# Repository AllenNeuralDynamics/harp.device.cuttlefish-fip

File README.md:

A [Cuttlefish](https://github.com/AllenNeuralDynamics/harp.device.cuttlefish) adapted to a dedicated fiber photometry application.

## Waveform Parameter Overview
This firmware generates the waveform below.

Multiple parameters are configurable:
* Continuous, or iterations
* software-trigger to start waveform generation
* `EVENT` message emitted upon rising edge of any camera trigger (configurable)

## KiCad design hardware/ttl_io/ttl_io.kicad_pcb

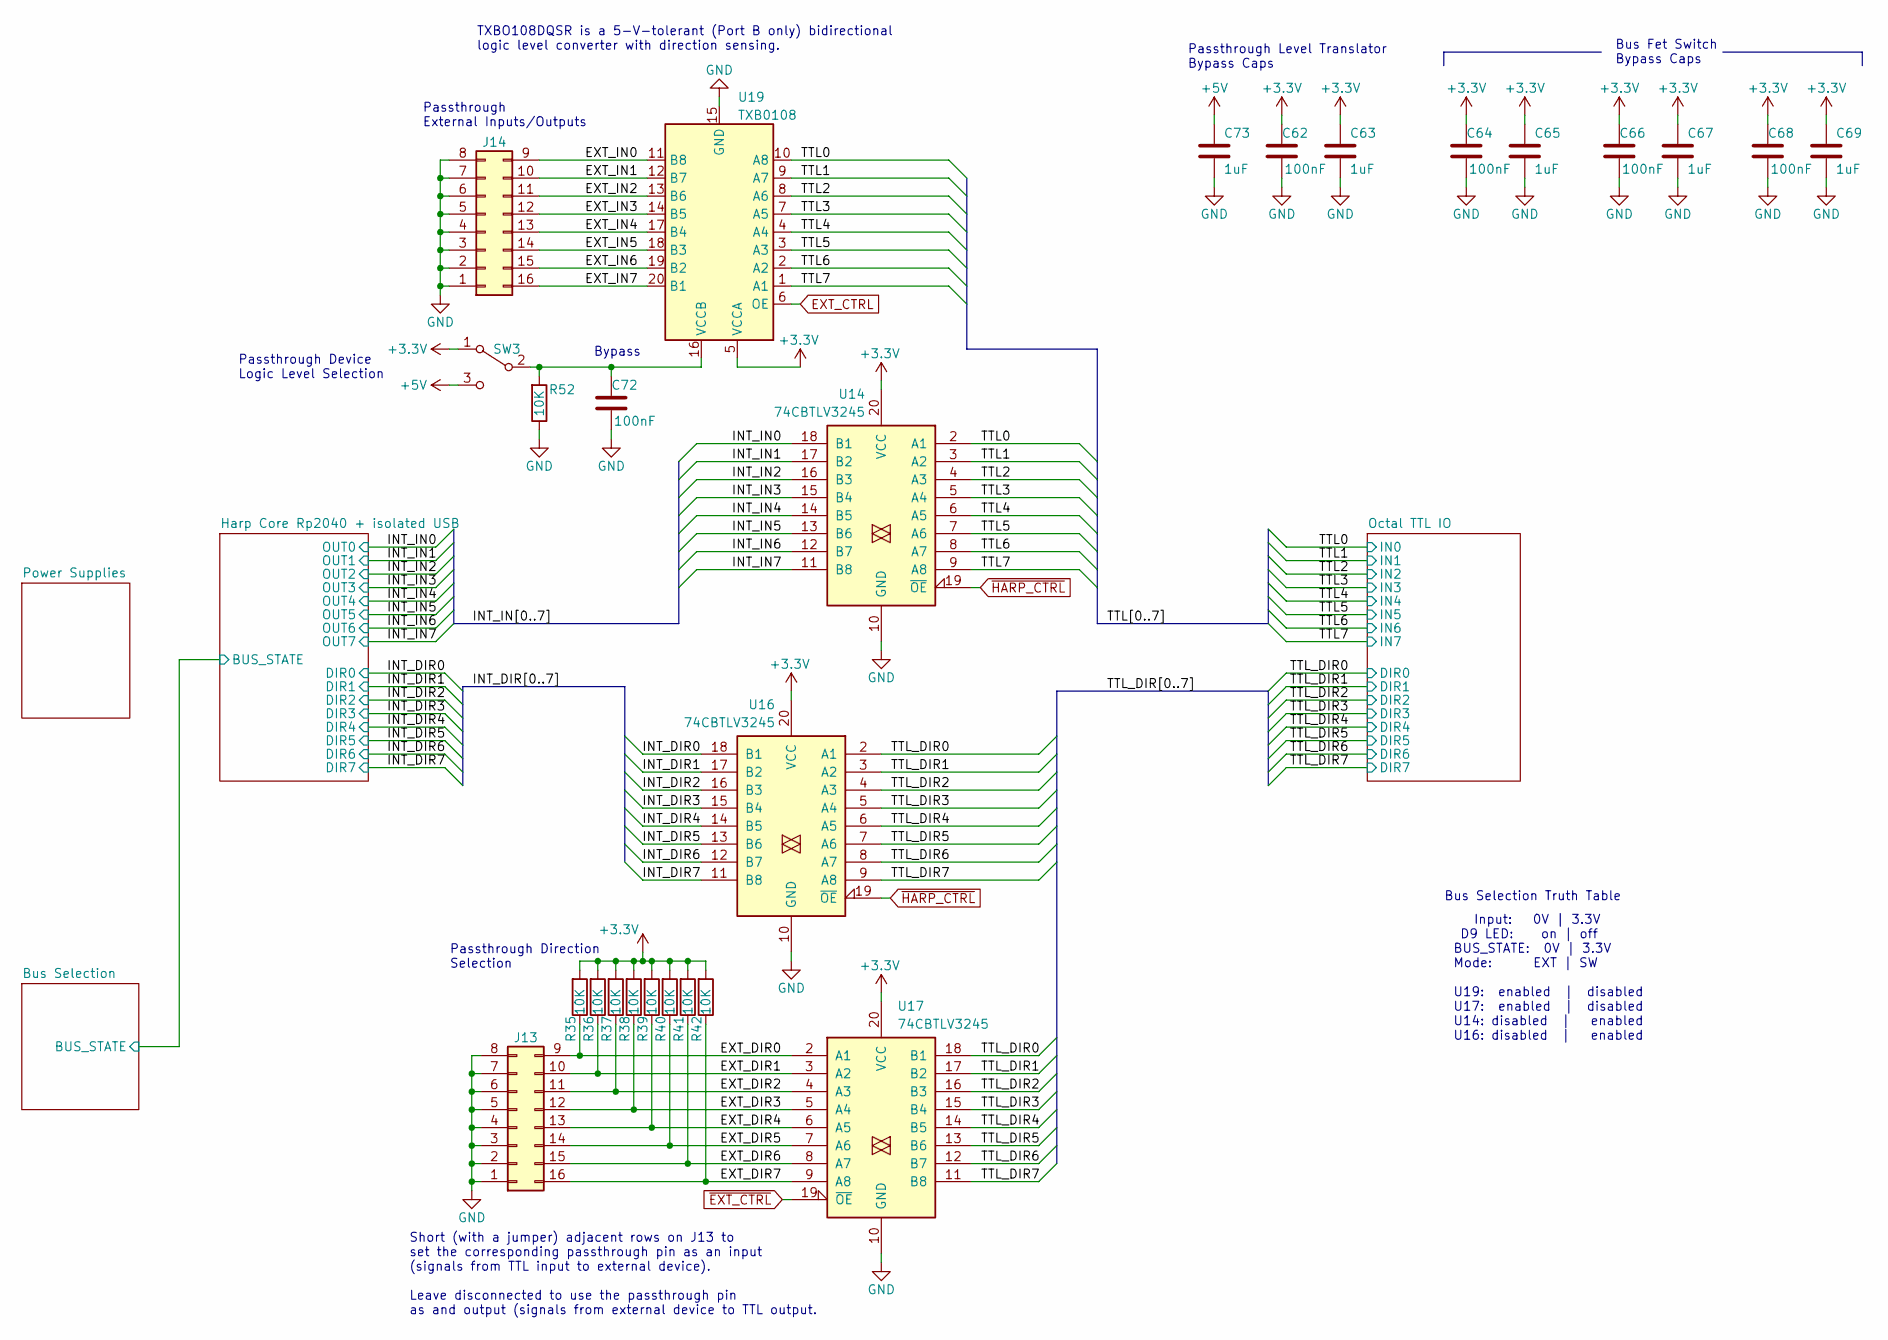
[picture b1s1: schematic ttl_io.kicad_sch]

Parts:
C62, C64, C66, C68, C72: 100nF; C_0402_1005Metric; Rated Voltage 16V; Tolerance 10%
C63, C65, C67, C69, C73: 1uF; C_0402_1005Metric; Rated Voltage 35V
J13, J14: Conn_02x08_Counter_Clockwise; PinHeader_2x08_P2.54mm_Horizontal_SMD
R35, R36, R37, R38, R39, R40, R41, R42, R52: 10K; R_0402_1005Metric
SW3: SW_SPDT; SW_SPDT_CK-JS102011SAQN
U14, U16, U17: 74CBTLV3245; TSSOP-20_4.4x6.5mm_P0.65mm
U19: TXB0108; TSSOP-20_4.4x6.5mm_P0.65mm

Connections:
+5V: C73.1, SW3.3 (C); also elsewhere on the board
/EXT_DIR0: J13.9, R35.1, U17.2 (A1)
/EXT_DIR1: J13.10, R36.1, U17.3 (A2)
/EXT_DIR2: J13.11, R37.1, U17.4 (A3)
/EXT_DIR3: J13.12, R38.1, U17.5 (A4)
/EXT_DIR4: J13.13, R39.1, U17.6 (A5)
/EXT_DIR5: J13.14, R40.1, U17.7 (A6)
/EXT_DIR6: J13.15, R41.1, U17.8 (A7)
/EXT_DIR7: J13.16, R42.1, U17.9 (A8)
/EXT_IN0: J14.9, U19.11 (B8)
/EXT_IN1: J14.10, U19.12 (B7)
/EXT_IN2: J14.11, U19.13 (B6)
/EXT_IN3: J14.12, U19.14 (B5)
/EXT_IN4: J14.13, U19.17 (B4)
/EXT_IN5: J14.14, U19.18 (B3)
/EXT_IN6: J14.15, U19.19 (B2)
/EXT_IN7: J14.16, U19.20 (B1)
/INT_DIR0: U16.18 (B1); also elsewhere on the board
/INT_DIR1: U16.17 (B2); also elsewhere on the board
/INT_DIR2: U16.16 (B3); also elsewhere on the board
/INT_DIR3: U16.15 (B4); also elsewhere on the board
/INT_DIR4: U16.14 (B5); also elsewhere on the board
/INT_DIR5: U16.13 (B6); also elsewhere on the board
/INT_DIR6: U16.12 (B7); also elsewhere on the board
/INT_DIR7: U16.11 (B8); also elsewhere on the board
/INT_IN0: U14.18 (B1); also elsewhere on the board
/INT_IN1: U14.17 (B2); also elsewhere on the board
/INT_IN2: U14.16 (B3); also elsewhere on the board
/INT_IN3: U14.15 (B4); also elsewhere on the board
/INT_IN4: U14.14 (B5); also elsewhere on the board
/INT_IN5: U14.13 (B6); also elsewhere on the board
/INT_IN6: U14.12 (B7); also elsewhere on the board
/INT_IN7: U14.11 (B8); also elsewhere on the board
/TTL0: U14.2 (A1), U19.10 (A8); also elsewhere on the board
/TTL1: U14.3 (A2), U19.9 (A7); also elsewhere on the board
/TTL2: U14.4 (A3), U19.8 (A6); also elsewhere on the board
/TTL3: U14.5 (A4), U19.7 (A5); also elsewhere on the board
/TTL4: U14.6 (A5), U19.4 (A4); also elsewhere on the board
/TTL5: U14.7 (A6), U19.3 (A3); also elsewhere on the board
/TTL6: U14.8 (A7), U19.2 (A2); also elsewhere on the board
/TTL7: U14.9 (A8), U19.1 (A1); also elsewhere on the board
/TTL_DIR0: U16.2 (A1), U17.18 (B1); also elsewhere on the board
/TTL_DIR1: U16.3 (A2), U17.17 (B2); also elsewhere on the board
/TTL_DIR2: U16.4 (A3), U17.16 (B3); also elsewhere on the board
/TTL_DIR3: U16.5 (A4), U17.15 (B4); also elsewhere on the board
/TTL_DIR4: U16.6 (A5), U17.14 (B5); also elsewhere on the board
/TTL_DIR5: U16.7 (A6), U17.13 (B6); also elsewhere on the board
/TTL_DIR6: U16.8 (A7), U17.12 (B7); also elsewhere on the board
/TTL_DIR7: U16.9 (A8), U17.11 (B8); also elsewhere on the board
EXT_CTRL: U19.6 (OE); also elsewhere on the board
GND: C62.1, C63.2, C64.1, C65.2, C66.1, C67.2, C68.1, C69.2, C72.1, C73.2, J13.1, J13.2, J13.3, J13.4, J13.5, J13.6, J13.7, J13.8, J14.1, J14.2, J14.3, J14.4, J14.5, J14.6, J14.7, J14.8, R52.1, U14.10 (GND), U16.10 (GND), U17.10 (GND), U19.15 (GND); also elsewhere on the board
unnamed: C72.2, R52.2, SW3.2 (B), U19.16 (VCCB)
~EXT_CTRL: U17.19 (~OE); also elsewhere on the board
~HARP_CTRL: U14.19 (~OE), U16.19 (~OE); also elsewhere on the board

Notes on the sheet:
Passthrough External Inputs/Outputs
Input: 0V | 3.3V D9 LED: on | off BUS_STATE: 0V | 3.3V Mode: EXT | SW U19: enabled | disabled U17: enabled | disabled U14: disabled | enabled U16: disabled | enabled
Passthrough Direction Selection
Bus Fet Switch Bypass Caps
TXBO108DQSR is a 5-V-tolerant (Port B only) bidirectional logic level converter with direction sensing.
Short (with a jumper) adjacent rows on J13 to set the corresponding passthrough pin as an input (signals from TTL input to external device). Leave disconnected to use the passthrough pin as and output (signals from external device to TTL output.
Passthrough Device Logic Level Selection
Bypass
Passthrough Level Translator Bypass Caps
Bus Selection Truth Table

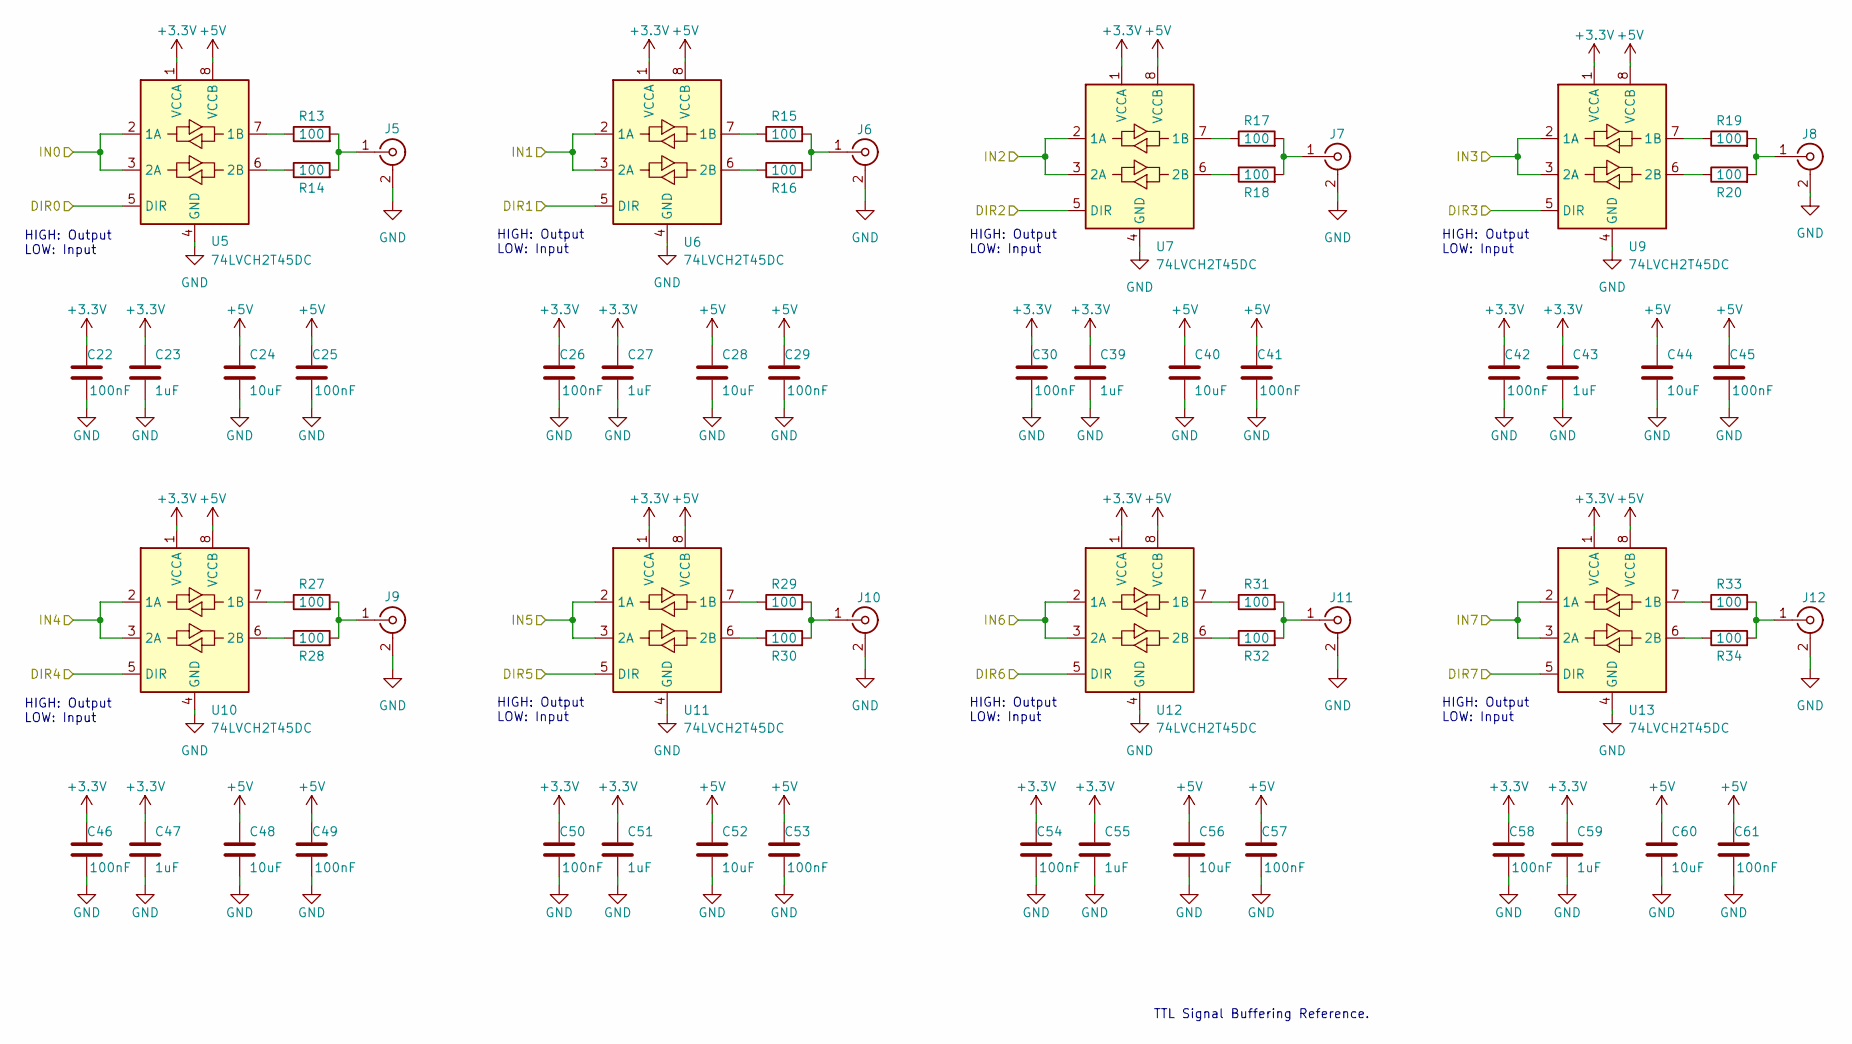
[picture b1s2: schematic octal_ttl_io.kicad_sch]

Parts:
C22, C25, C26, C29, C30, C41, C42, C45, C46, C49, C50, C53, C54, C57, C58, C61: 100nF; C_0402_1005Metric; Rated Voltage 16V; Tolerance 10%
C23, C27, C39, C43, C47, C51, C55, C59: 1uF; C_0402_1005Metric; Rated Voltage 35V
C24, C28, C40, C44, C48, C52, C56, C60: 10uF; C_0805_2012Metric; Rated Voltage 25V
J5, J6, J7, J8, J9, J10, J11, J12: Conn_Coaxial; BNC_AmphenolRF_031-5329-52RFX_Vertical
R13, R14, R15, R16, R17, R18, R19, R20, R27, R28, R29, R30, R31, R32, R33, R34: 100; R_0402_1005Metric; Tolerance 1%
U5, U6, U7, U9, U10, U11, U12, U13: 74LVCH2T45DC; VSSOP-8_2.3x2mm_P0.5mm

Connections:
+5V: C24.1, C25.2, C28.1, C29.2, C40.1, C41.2, C44.1, C45.2, C48.1, C49.2, C52.1, C53.2, C56.1, C57.2, C60.1, C61.2, U5.8 (VCCB), U6.8 (VCCB), U7.8 (VCCB), U9.8 (VCCB), U10.8 (VCCB), U11.8 (VCCB), U12.8 (VCCB), U13.8 (VCCB); also elsewhere on the board
/TTL0: U5.2 (1A), U5.3 (2A); also elsewhere on the board
/TTL1: U6.2 (1A), U6.3 (2A); also elsewhere on the board
/TTL2: U7.2 (1A), U7.3 (2A); also elsewhere on the board
/TTL3: U9.2 (1A), U9.3 (2A); also elsewhere on the board
/TTL4: U10.2 (1A), U10.3 (2A); also elsewhere on the board
/TTL5: U11.2 (1A), U11.3 (2A); also elsewhere on the board
/TTL6: U12.2 (1A), U12.3 (2A); also elsewhere on the board
/TTL7: U13.2 (1A), U13.3 (2A); also elsewhere on the board
/TTL_DIR0: U5.5 (DIR); also elsewhere on the board
/TTL_DIR1: U6.5 (DIR); also elsewhere on the board
/TTL_DIR2: U7.5 (DIR); also elsewhere on the board
/TTL_DIR3: U9.5 (DIR); also elsewhere on the board
/TTL_DIR4: U10.5 (DIR); also elsewhere on the board
/TTL_DIR5: U11.5 (DIR); also elsewhere on the board
/TTL_DIR6: U12.5 (DIR); also elsewhere on the board
/TTL_DIR7: U13.5 (DIR); also elsewhere on the board
GND: C22.1, C23.2, C24.2, C25.1, C26.1, C27.2, C28.2, C29.1, C30.1, C39.2, C40.2, C41.1, C42.1, C43.2, C44.2, C45.1, C46.1, C47.2, C48.2, C49.1, C50.1, C51.2, C52.2, C53.1, C54.1, C55.2, C56.2, C57.1, C58.1, C59.2, C60.2, C61.1, J5.2 (Ext), J6.2 (Ext), J7.2 (Ext), J8.2 (Ext), J9.2 (Ext), J10.2 (Ext), J11.2 (Ext), J12.2 (Ext), U5.4 (GND), U6.4 (GND), U7.4 (GND), U9.4 (GND), U10.4 (GND), U11.4 (GND), U12.4 (GND), U13.4 (GND); also elsewhere on the board
unnamed: J5.1 (In), R13.2, R14.2
unnamed: J6.1 (In), R15.2, R16.2
unnamed: J7.1 (In), R17.2, R18.2
unnamed: J8.1 (In), R19.2, R20.2
unnamed: J9.1 (In), R27.2, R28.2
unnamed: J10.1 (In), R29.2, R30.2
unnamed: J11.1 (In), R31.2, R32.2
unnamed: J12.1 (In), R33.2, R34.2
unnamed: R13.1, U5.7 (1B)
unnamed: R14.1, U5.6 (2B)
unnamed: R15.1, U6.7 (1B)
unnamed: R16.1, U6.6 (2B)
unnamed: R17.1, U7.7 (1B)
unnamed: R18.1, U7.6 (2B)
unnamed: R19.1, U9.7 (1B)
unnamed: R20.1, U9.6 (2B)
unnamed: R27.1, U10.7 (1B)
unnamed: R28.1, U10.6 (2B)
unnamed: R29.1, U11.7 (1B)
unnamed: R30.1, U11.6 (2B)
unnamed: R31.1, U12.7 (1B)
unnamed: R32.1, U12.6 (2B)
unnamed: R33.1, U13.7 (1B)
unnamed: R34.1, U13.6 (2B)

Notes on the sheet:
HIGH: Output LOW: Input
TTL Signal Buffering Reference.

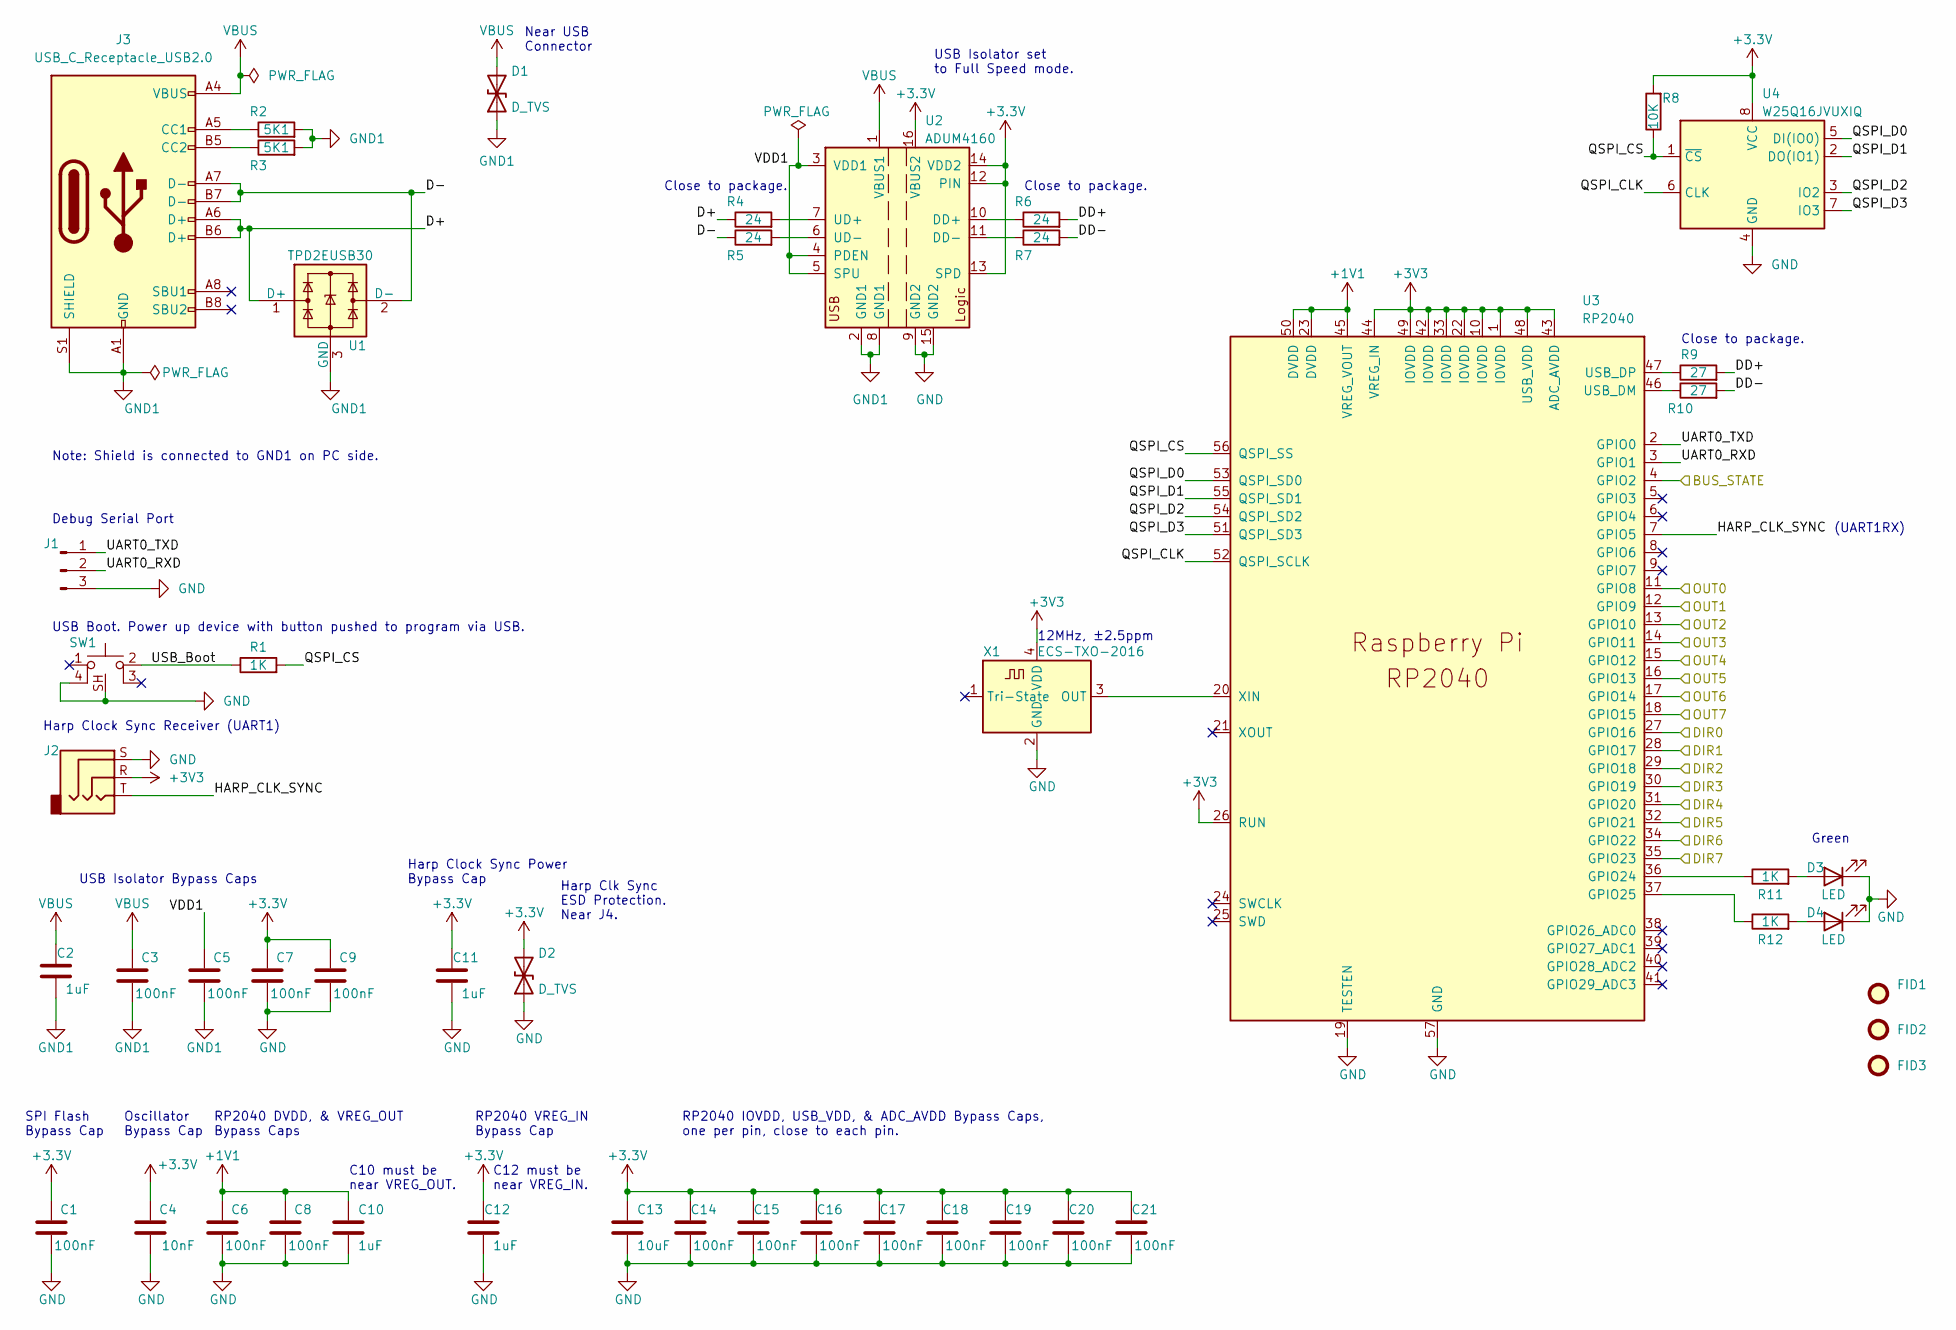
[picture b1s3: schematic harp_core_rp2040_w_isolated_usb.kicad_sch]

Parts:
C1, C3, C5, C6, C7, C8, C9, C14, C15, C16, C17, C18, C19, C20, C21: 100nF; C_0402_1005Metric; Rated Voltage 16V; Tolerance 10%
C2, C10, C11, C12: 1uF; C_0402_1005Metric; Rated Voltage 35V
C4: 10nF; C_0402_1005Metric; Rated Voltage 25V; Tolerance 10%
C13: 10uF; C_0805_2012Metric; Rated Voltage 25V
D1, D2: D_TVS; D_0402_1005Metric
D3, D4: LED; LED_0603_1608Metric
FID1, FID2, FID3: Fiducial; Fiducial_0.5mm_Mask1mm
J1: Conn_01x03_Male; PinHeader_1x03_P2.54mm_Vertical
J2: AudioJack3; Jack_3.5mm_CUI_SJ-3523-SMT_Horizontal
J3: USB_C_Receptacle_USB2.0; USB_C_Receptacle_JAE_DX07S016JA1R1500
R1, R11, R12: 1K; R_0402_1005Metric; Tolerance 1%
R2, R3: 5K1; R_0402_1005Metric; Tolerance 1%
R4, R5, R6, R7: 24; R_0402_1005Metric; Tolerance 1%
R8: 10K; R_0402_1005Metric
R9, R10: 27; R_0402_1005Metric; Tolerance 1%
SW1: SW_Push_1P1T-SH_NO_Vertical_Wuerth_WS-TASV
U1: TPD2EUSB30; Texas_DRT-3
U2: ADUM4160; SOIC-16W_7.5x10.3mm_P1.27mm
U3: RP2040; RP2040-QFN-56
U4: W25Q16JVUXIQ; Winbond-8USON-2x3mm
X1: ECS-TXO-2016; Crystal_SMD_2016-4Pin_2.0x1.6mm; Tolerance ±2.5ppm

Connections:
+1V1: C6.2, C8.2, C10.1, U3.23 (DVDD), U3.45 (VREG_VOUT), U3.50 (DVDD)
/Bus Selection/BUS_STATE: U3.4 (GPIO2); also elsewhere on the board
/Harp Core Rp2040 + isolated USB/D+: J3.A6 (D+), J3.B6 (D+), R4.1, U1.1 (D+)
/Harp Core Rp2040 + isolated USB/D-: J3.A7 (D-), J3.B7 (D-), R5.1, U1.2 (D-)
/Harp Core Rp2040 + isolated USB/DD+: R6.2, R9.2
/Harp Core Rp2040 + isolated USB/DD-: R7.2, R10.2
/Harp Core Rp2040 + isolated USB/HARP_CLK_SYNC: J2.T, U3.7 (GPIO5)
/Harp Core Rp2040 + isolated USB/QSPI_CLK: U3.52 (QSPI_SCLK), U4.6 (CLK)
/Harp Core Rp2040 + isolated USB/QSPI_CS: R1.2, R8.1, U3.56 (QSPI_SS), U4.1 (~CS)
/Harp Core Rp2040 + isolated USB/QSPI_D0: U3.53 (QSPI_SD0), U4.5 (DI(IO0))
/Harp Core Rp2040 + isolated USB/QSPI_D1: U3.55 (QSPI_SD1), U4.2 (DO(IO1))
/Harp Core Rp2040 + isolated USB/QSPI_D2: U3.54 (QSPI_SD2), U4.3 (IO2)
/Harp Core Rp2040 + isolated USB/QSPI_D3: U3.51 (QSPI_SD3), U4.7 (IO3)
/Harp Core Rp2040 + isolated USB/UART0_RXD: J1.2, U3.3 (GPIO1)
/Harp Core Rp2040 + isolated USB/UART0_TXD: J1.1, U3.2 (GPIO0)
/Harp Core Rp2040 + isolated USB/USB_Boot: R1.1, SW1.2
/Harp Core Rp2040 + isolated USB/VDD1: C5.2, U2.3 (VDD1), U2.4 (PDEN), U2.5 (SPU)
/INT_DIR0: U3.27 (GPIO16); also elsewhere on the board
/INT_DIR1: U3.28 (GPIO17); also elsewhere on the board
/INT_DIR2: U3.29 (GPIO18); also elsewhere on the board
/INT_DIR3: U3.30 (GPIO19); also elsewhere on the board
/INT_DIR4: U3.31 (GPIO20); also elsewhere on the board
/INT_DIR5: U3.32 (GPIO21); also elsewhere on the board
/INT_DIR6: U3.34 (GPIO22); also elsewhere on the board
/INT_DIR7: U3.35 (GPIO23); also elsewhere on the board
/INT_IN0: U3.11 (GPIO8); also elsewhere on the board
/INT_IN1: U3.12 (GPIO9); also elsewhere on the board
/INT_IN2: U3.13 (GPIO10); also elsewhere on the board
/INT_IN3: U3.14 (GPIO11); also elsewhere on the board
/INT_IN4: U3.15 (GPIO12); also elsewhere on the board
/INT_IN5: U3.16 (GPIO13); also elsewhere on the board
/INT_IN6: U3.17 (GPIO14); also elsewhere on the board
/INT_IN7: U3.18 (GPIO15); also elsewhere on the board
GND: C1.1, C4.1, C6.1, C7.1, C8.1, C9.1, C10.2, C11.2, C12.2, C13.2, C14.1, C15.1, C16.1, C17.1, C18.1, C19.1, C20.1, C21.1, D2.1 (A1), D3.1 (K), D4.1 (K), J1.3, J2.S, SW1.4, SW1.SH, U2.9 (GND2), U2.15 (GND2), U3.19 (TESTEN), U3.57 (GND), U4.4 (GND), X1.2 (GND); also elsewhere on the board
GND1: C2.2, C3.1, C5.1, D1.1 (A1), J3.A1 (GND), J3.A12 (GND), J3.B1 (GND), J3.B12 (GND), J3.S1 (SHIELD), R2.2, R3.2, U1.3 (GND), U2.2 (GND1), U2.8 (GND1)
unnamed: D3.2 (A), R11.2
unnamed: D4.2 (A), R12.2
unnamed: J3.A5 (CC1), R2.1
unnamed: J3.B5 (CC2), R3.1
unnamed: R6.1, U2.10 (DD+)
unnamed: R7.1, U2.11 (DD-)
unnamed: R4.2, U2.7 (UD+)
unnamed: R5.2, U2.6 (UD-)
unnamed: R11.1, U3.36 (GPIO24)
unnamed: R12.1, U3.37 (GPIO25)
unnamed: R10.1, U3.46 (USB_DM)
unnamed: R9.1, U3.47 (USB_DP)
unnamed: U3.20 (XIN), X1.3 (OUT)
VBUS: C2.1, C3.2, D1.2 (A2), J3.A4 (VBUS), J3.A9 (VBUS), J3.B4 (VBUS), J3.B9 (VBUS), U2.1 (VBUS1)

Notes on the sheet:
USB Isolator Bypass Caps
Near USB Connector
Close to package.
Harp Clock Sync Power Bypass Cap
USB Isolator set to Full Speed mode.
12MHz, ±2.5ppm
Debug Serial Port
USB Boot. Power up device with button pushed to program via USB.
(UART1RX)
Harp Clock Sync Receiver (UART1)
Note: Shield is connected to GND1 on PC side.
RP2040 DVDD, & VREG_OUT Bypass Caps
RP2040 IOVDD, USB_VDD, & ADC_AVDD Bypass Caps, one per pin, close to each pin.
C10 must be near VREG_OUT.
RP2040 VREG_IN Bypass Cap
SPI Flash Bypass Cap
Harp Clk Sync ESD Protection. Near J4.
Oscillator Bypass Cap
C12 must be near VREG_IN.
Green

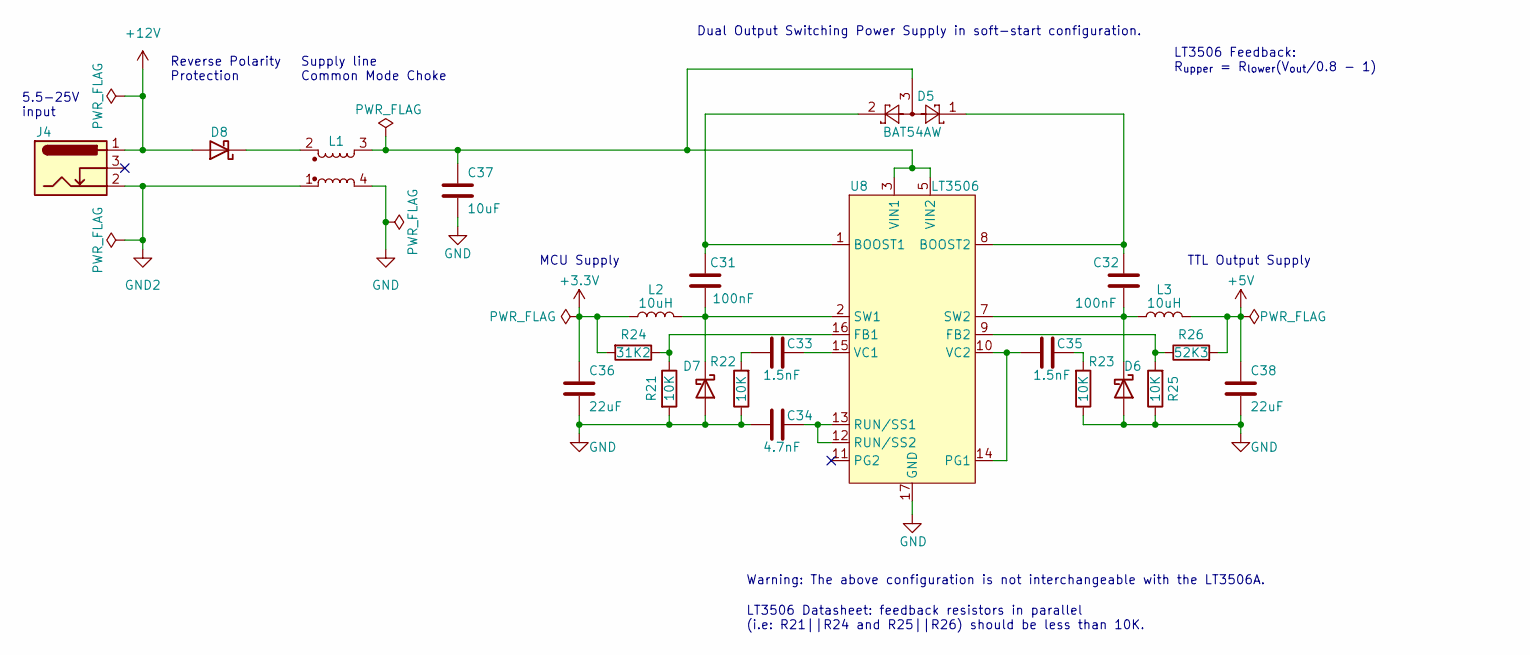
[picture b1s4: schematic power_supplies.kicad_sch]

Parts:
C31, C32: 100nF; C_0402_1005Metric; Rated Voltage 16V; Tolerance 10%
C33: 1.5nF; R_0402_1005Metric; Tolerance 10%; Voltage Rating 50V
C34: 4.7nF; R_0402_1005Metric; Tolerance 10%; Voltage Rating 50V
C35: 1.5nF; R_0402_1005Metric; Tolerance 10%
C36, C38: 22uF; C_0805_2012Metric; Rated Voltage 25V
C37: 10uF; C_0805_2012Metric; Rated Voltage 25V
D5: BAT54AW; SOT-323_SC-70
D6, D7, D8: D_Schottky; D_SOD-123
J4: Barrel_Jack_Switch; BarrelJack_CUI_PJ-102AH_Horizontal
L1: L_Coupled_1423; L_CommonModeChoke_TDKCorporation_1210
L2, L3: 10uH; L_Vishay_IHLP-2525
R21, R22, R23, R25: 10K; R_0402_1005Metric
R24: 31K2; R_0402_1005Metric; Tolerance 1%
R26: 52K3; R_0402_1005Metric; Tolerance 1%
U8: LT3506; DFN-16-1EP_4x5mm_P0.5mm_EP2.44x4.34mm

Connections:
+5V: C38.1, L3.2, R26.2; also elsewhere on the board
+12V: D8.2 (A), J4.1
GND: C34.1, C36.2, C37.2, C38.2, D6.2 (A), D7.2 (A), L1.4, R21.2, R22.1, R23.1, R25.1, U8.17 (GND); also elsewhere on the board
GND2: J4.2, L1.1
unnamed: C33.1, R22.2
unnamed: C35.2, R23.2
unnamed: C32.1, D6.1 (K), L3.1, U8.7 (SW2)
unnamed: C31.1, D7.1 (K), L2.2, U8.2 (SW1)
unnamed: D8.1 (K), L1.2
unnamed: C31.2, D5.2, U8.1 (BOOST1)
unnamed: C32.2, D5.1, U8.8 (BOOST2)
unnamed: R21.1, R24.1, U8.16 (FB1)
unnamed: R25.2, R26.1, U8.9 (FB2)
unnamed: C35.1, U8.10 (VC2), U8.14 (PG1)
unnamed: C34.2, U8.12 (RUN/SS2), U8.13 (RUN/SS1)
unnamed: C33.2, U8.15 (VC1)
VIN1: C37.1, D5.3, L1.3, U8.3 (VIN1), U8.4 (VIN1), U8.5 (VIN2), U8.6 (VIN2)

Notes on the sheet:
Reverse Polarity Protection
LT3506 Datasheet: feedback resistors in parallel (i.e: R21||R24 and R25||R26) should be less than 10K.
TTL Output Supply
Supply line Common Mode Choke
Dual Output Switching Power Supply in soft-start configuration.
LT3506 Feedback: R_{upper} = R_{lower}(V_{out}/0.8 - 1)
Warning: The above configuration is not interchangeable with the LT3506A.
MCU Supply
5.5-25V input

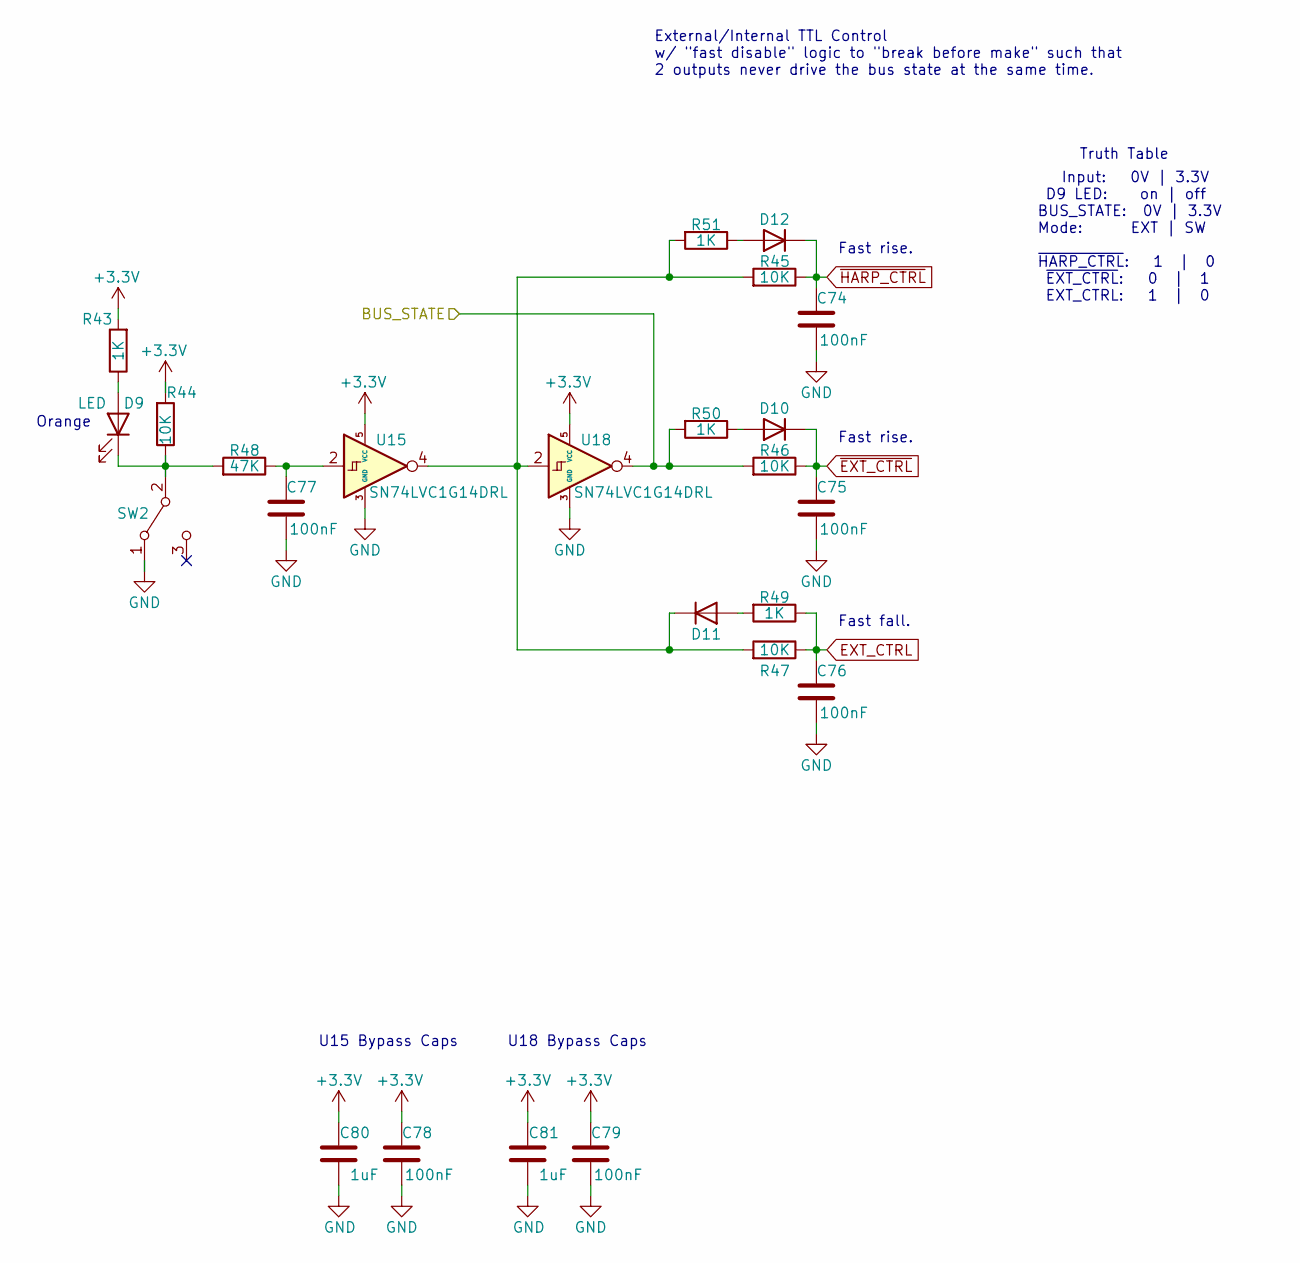
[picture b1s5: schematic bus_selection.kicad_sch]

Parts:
C74, C75, C76, C77, C78, C79: 100nF; C_0402_1005Metric; Rated Voltage 16V; Tolerance 10%
C80, C81: 1uF; C_0402_1005Metric; Rated Voltage 35V
D9: LED; LED_0603_1608Metric
D10, D11, D12: NSR05F40NXT5G; D_0402_1005Metric
R43, R49, R50, R51: 1K; R_0402_1005Metric; Tolerance 1%
R44, R45, R46, R47: 10K; R_0402_1005Metric
R48: 47K; R_0402_1005Metric; Tolerance 1%
SW2: SW_SPDT; SW_SPDT_CK-JS102011SAQN
U15, U18: SN74LVC1G14DRL; SOT-553

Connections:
/Bus Selection/BUS_STATE: R46.2, R50.2, U18.4; also elsewhere on the board
EXT_CTRL: C76.2, R47.1, R49.1; also elsewhere on the board
GND: C74.1, C75.1, C76.1, C77.1, C78.1, C79.1, C80.2, C81.2, SW2.1 (A), U15.3 (GND), U18.3 (GND); also elsewhere on the board
unnamed: C77.2, R48.1, U15.2
unnamed: D9.2 (A), R43.1
unnamed: D9.1 (K), R44.1, R48.2, SW2.2 (B)
unnamed: D10.2 (A), R50.1
unnamed: D11.2 (A), R49.2
unnamed: D11.1 (K), R45.2, R47.2, R51.2, U15.4, U18.2
unnamed: D12.2 (A), R51.1
~EXT_CTRL: C75.2, D10.1 (K), R46.1; also elsewhere on the board
~HARP_CTRL: C74.2, D12.1 (K), R45.1; also elsewhere on the board

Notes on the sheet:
Truth Table
External/Internal TTL Control w/ "fast disable" logic to "break before make" such that 2 outputs never drive the bus state at the same time.
U18 Bypass Caps
Input: 0V | 3.3V D9 LED: on | off BUS_STATE: 0V | 3.3V Mode: EXT | SW ~{HARP_CTRL}: 1 | 0 ~{EXT_CTRL}: 0 | 1 EXT_CTRL: 1 | 0
U15 Bypass Caps
Fast fall.
Fast rise.
Orange

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
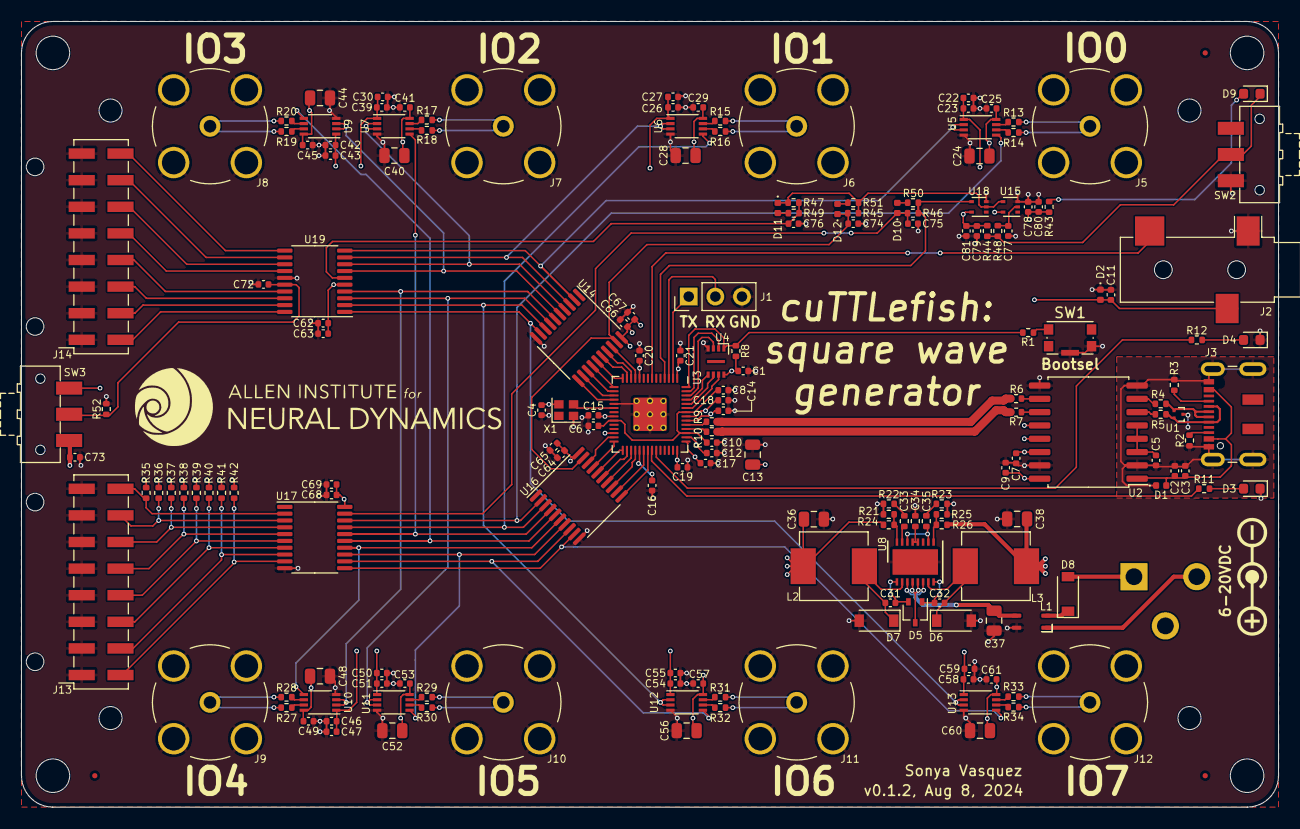
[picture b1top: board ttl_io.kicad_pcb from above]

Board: 4 copper layers, 120.0 x 75.0 mm, 188 parts (1 on the bottom side), 133 nets.

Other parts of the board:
G2, G3: LOGO

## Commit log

2023-10-04 initial commit; draft schematic
2023-10-04 draft mcu bypass with bus switches
2023-10-05 update schematic with bus switches
2023-10-28 update passthrough level translator
2023-12-22 update layout
2024-01-02 update power supply schematic/board
2024-01-02 annotate bus logic on schematic
2024-01-03 update pcb
2024-01-05 draft pcb v0.1.0
2024-01-12 update pcb and bom
2024-01-12 add hw/fw licenses
2024-01-13 draft firmware
2024-01-18 draft scheduler
2024-01-19 split scheduler and schedulees into separate classes
2024-01-19 draft scheduler and schedulees
2024-01-20 draft scheduler; compiles
2024-01-22 crude pwm blink task works
2024-01-23 reference wrapper rewrite; get multiple tasks working
2024-01-24 enable queueing multiple alarms
2024-01-27 add pin mask and cpu profiling
2024-01-27 pwm mask demo
2024-01-28 invoke irq directly; make schedule work up to 100KHz
2024-02-01 move scheduler to core1
2024-02-12 enable starting waveform from harp msg
2024-02-12 enable killing/restarting schedule
2024-02-12 update comment
2024-02-13 add step file
2024-02-13 add enclosure cad model
2024-02-13 update enclosure
2024-02-14 enable direct gpio writing
2024-02-14 add nops to handle slew rate
2024-02-14 enable resetting schedule
2024-02-14 add extra example
2024-02-15 update case cad with laser cut offsets
2024-02-16 update enclosure wall clearances
2024-02-16 update test waveforms in pyharp test
2024-02-17 draft fifo strategy
2024-03-25 Add device.yml
2024-03-25 Add solution structure
2024-03-25 Fix file
2024-03-25 Regenerate package
2024-03-25 Add helper method to configure PWM
2024-06-21 add extra registers; stub behavior
2024-06-21 update send many example with correct registers
2024-07-24 append git hash to executable name
2024-07-30 Bump release
2024-08-08 enable external pin to trigger schedule
2024-08-08 add externally-triggered waveform example
2024-08-09 implement finite pulses
2024-08-12 get pwm task and ios working
2024-08-30 get sw start-immediately working
2024-11-08 Update bonsai generators
2024-11-09 Fix schema source
2024-11-10 Favor harp-tech as source of device schema
2025-03-18 update readme; submodule pwm lib
2025-03-19 draft task base class and pulse train task
2025-03-20 draft pulsetrain task
2025-03-20 make event times absolute intervals
2025-03-21 draft working pwm task
2025-03-22 add barebones fip schedule
2025-03-28 get fip schedule looping
2025-03-28 draft working fip schedule
2025-04-04 draft minimal laser-fip-task-centric approach
2025-04-04 draft app registers and handler fns
2025-04-04 flesh out reg read/write funcs
2025-04-07 cleanup file layout
2025-04-08 scaffold receiving messages on core1
2025-04-10 Update harp.core.rp2040 to latest commit on main
2025-04-10 Set up multicore communication
2025-04-10 get draft compiling
2025-04-10 add first pyharp test
2025-04-10 write send many fip waveform tests
2025-04-11 bugfix pwm re-init
2025-04-17 Add initial draft
2025-04-17 configure cuttelfish bus switches for sw control.
2025-04-18 Fix small typos
2025-04-18 Add first draft of bonsai interface
2025-04-21 Add description to operators
2025-04-21 translate PCB output to GPIO output
2025-04-21 make device disable upon entering STANDBY op mode.
2025-04-22 fix rising edge output gpio offset
2025-04-22 add test for delta time measurements for rising edge events
2025-04-25 Make non-flag like bitMask a groupMask
2025-04-25 Fix project title
2025-04-30 fix laser base address calculation
2025-04-30 fix task removal logic and update task settings registers
2025-04-30 fix PWM pin and output mask offsets in laser task reconfiguration
2025-04-30 add test for configuring removing tasks
2025-04-30 update FIP device ID and set whoAmI to 1407
2025-04-30 make laser task pin one-hot encoded
2025-05-07 fix: convert rising edge tstamp to harp clock domain
2025-05-08 Make ClearAllTasks interface a standard EnableFlag type
2025-05-08 Document TaskRisingEdgeEvent register
2025-05-08 Regenerate bonsai interface
2025-06-03 refactor: replace EnableTaskSchedule with SetTasksState and add abort functionality
2025-06-03 replace EnableTaskSchedule with SetTasksState in pyharp tests
2025-06-03 add test for aborting tasks
2025-06-03 Fix typo
2025-06-03 Update generators
2025-06-03 Regenerate device
2025-06-03 Add interface to task state register
2025-06-28 Use TasksState enum for better clarity
2025-06-28 Update test script to print nominal delta-T and error values
2025-06-28 Improve register description
2025-06-28 Prepare for first release
